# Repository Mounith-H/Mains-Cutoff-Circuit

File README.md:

# Mains High-Low Voltage Cutoff Circuit 🔌

A hardware circuit designed to automatically disconnect mains power during overvoltage (>270V) or undervoltage (<170V) conditions to protect appliances.

---

## Table of Contents
- [Features](#features)
- [Components](#components)
- [Circuit Diagram](#circuit-diagram)
- [How It Works](#how-it-works)
- [Usage](#usage)
- [Safety Notes](#safety-notes)
- [License](#license)
- [Contributing](#contributing)

---

## Features ✨
- **Auto Cutoff**: Disconnects power during voltage fluctuations.
- **4 LED Indicators**: 
  - 1 OverVoltage LED: RED for input has voltage above set threshold, Green for normal.
  - 2 UnderVoltage LED: RED for input has voltage below set threshold, Green for normal.
  - 3 Delay LED: RED for in delay mode.
  - 4 Output LED: RED Output OFF, GREEN Output ON.
- **DELAY ON/OFF**: jumper(J6)) to Enable/Desable dealy.
- **Relay-Based**: Supports high-current loads.

---

## Components 🛠️

| Designators               | Component                      | Footprint                                      | Quantity |  
|---------------------------|--------------------------------|-----------------------------------------------|----------|
| R5, R21, R22, R28, R24, R18 | 10k Resistor                  | Axial DIN0207 (6.3mm x 2.5mm)                | 6        |
| R15, R13, R10, R6, R19, R9, R20, R7, R12, R23, R16 | 1k Resistor          | Axial DIN0207 (6.3mm x 2.5mm)                | 11       |
| U1                        | LM324 Op-Amp IC               | CERDIP-14 (Side-Brazed Socket)               | 1        |
| R17, R11, R14, R8         | 220Ω Resistor                 | Axial DIN0207 (6.3mm x 2.5mm)                | 4        |
| Q4, Q3, Q7, Q2, Q1, Q6    | BC547 Transistor              | TO-92L Wide Package                          | 6        |
| D6, D8, D9, D7            | Dual LED                      | LED D3.0mm-3                                 | 4        |
| D5, D11, D3, D4           | 1N4148 Diode                  | DO-35 Horizontal                             | 4        |
| R4, R25, R2               | 16k Resistor                  | Axial DIN0207 (6.3mm x 2.5mm)                | 3        |
| J4                        | LED Board Header              | 1x06 Pin Header (2.54mm)                     | 1        |
| R1                        | 1.5k Resistor                 | Axial DIN0207 (6.3mm x 2.5mm)                | 1        |
| C2                        | 1µF Capacitor                 | Radial D5.0mm (P2.50mm)                      | 1        |
| RV2, RV1, RV3             | 10k Potentiometer             | Bourns 3296W Vertical Trimmer                | 3        |
| PS1                       | Hi-Link 12V Power Supply      | HLK-5M05 Module                              | 1        |
| D10, D2, D1               | 1N4007 Diode                  | DO-41 Horizontal                             | 3        |
| RV4                       | 5k Potentiometer              | Bourns 3296W Vertical Trimmer                | 1        |
| R26                       | 470k Resistor                 | Axial DIN0207 (6.3mm x 2.5mm)                | 1        |
| C3                        | 100µF Capacitor               | Radial D6.3mm (P2.50mm)                      | 1        |
| F1                        | Fuse                          | Blade ATO (Direct Solder)                    | 1        |
| J2                        | Transformer Terminal Block    | 1x03 Terminal Block (5.00mm)                 | 1        |
| J1, J5                    | AC Input Terminal Block       | Phoenix PT-1.5-2-5.0-H (5.00mm)              | 2        |
| R27                       | 0Ω Jumper Resistor            | Axial DIN0207 (6.3mm x 2.5mm)                | 1        |
| K1                        | Relay (SPDT)                  | SANYOU SRD Series Form-C                     | 1        |
| C1, C4                    | 100nF Capacitor               | 1210 SMD (Hand-Soldered)                     | 2        |
| U2                        | LM78M05 Voltage Regulator     | TO-252-2 Package                             | 1        |

---

## How It Works ⚙️
AC Input → Voltage Sensing → Threshold Comparison → Relay Control → Load Protection  

**Step-by-Step Explanation**

1. AC Input & Isolation
- Mains power (e.g., 220V AC) enters through terminal blocks J1/J5.
- A transformer (connected via J2) steps down the voltage to 12V AC for safe sensing.
- The Hi-Link 12V module (PS1) converts this to 12V DC, while the LM78M05 (U2) regulates it to 5V DC for the control circuitry.

2. Voltage Sensing
- The AC voltage is scaled down using a resistor network (R1, R2, R4, R25, RV1, RV2).
- Potentiometers RV1 and RV2 set the overvoltage (e.g., >270V) and undervoltage (e.g., <170V) thresholds.

3. Threshold Comparison
- The LM324 op-amp (U1) acts as a comparator:
    - One section compares the sensed voltage to the high threshold (set by RV1).
    - Another section compares it to the low threshold (set by RV2).
- If the voltage exceeds either threshold, the LM324 triggers a fault signal.

4. Relay Control
- Fault signals drive BC547 transistors (Q1-Q6) to deactivate the SPDT relay (K1).
- The relay disconnects the load from mains power to prevent damage.

5. Status Indication
- Dual LEDs (D6-D9) indicate system status:
    - Green: Normal operation (voltage within range).
    - Red: Error detected.

- The 470k resistor (R26) and 100µF capacitor (C3) introduce a delay to avoid false triggering.

---

## Usage 🚀  
1. **Power Up**:  
   - Connect mains power to `J1` and load to relay output `J5`.  
2. **Normal Operation**:  
   - **Green LED**: Voltage within safe range (170V–270V).  
3. **Fault Detection**:  
   - **Red LED**: Overvoltage/Undervoltage detected (>270V) or (<170V).  
   - Relay disconnects load automatically.  
4. **Reset**:  
   - **Auto-reset**: Wait for delay (adjustable via `RV4`).  
   - **Manual reset**: Remove short on `J6` pins to restore power immediately.  

---

## Safety Notes ⚠️  
- **High Voltage Risk!** This circuit interacts with mains power.  
  - Use insulated tools and enclosures.  
  - Test with a low-voltage (12V AC) source before connecting to mains.  
- **Fuse Protection**: Ensure `F1` matches your load’s current rating.  
- **No Live Adjustments**: Always power off before adjusting `RV1/RV2/RV3`.  
- **Secure Connections**: Double-check terminal blocks (`J1/J5`) and transformer wiring.  

### Created by [Mounith H] – 📧 mounith.h@gmail.com

## License 📄  
```text
MIT License

Copyright (c) 2023 [Your Name]

Permission is hereby granted, free of charge, to any person obtaining a copy
of this software and associated documentation files (the "Software"), to deal
in the Software without restriction, including without limitation the rights
to use, copy, modify, merge, publish, distribute, sublicense, and/or sell
copies of the Software, and to permit persons to whom the Software is
furnished to do so, subject to the following conditions:

The above copyright notice and this permission notice shall be included in all
copies or substantial portions of the Software.

THE SOFTWARE IS PROVIDED "AS IS", WITHOUT WARRANTY OF ANY KIND, EXPRESS OR
IMPLIED, INCLUDING BUT NOT LIMITED TO THE WARRANTIES OF MERCHANTABILITY,
FITNESS FOR A PARTICULAR PURPOSE AND NONINFRINGEMENT. IN NO EVENT SHALL THE
AUTHORS OR COPYRIGHT HOLDERS BE LIABLE FOR ANY CLAIM, DAMAGES OR OTHER
LIABILITY, WHETHER IN AN ACTION OF CONTRACT, TORT OR OTHERWISE, ARISING FROM,
OUT OF OR IN CONNECTION WITH THE SOFTWARE OR THE USE OR OTHER DEALINGS IN THE
SOFTWARE.

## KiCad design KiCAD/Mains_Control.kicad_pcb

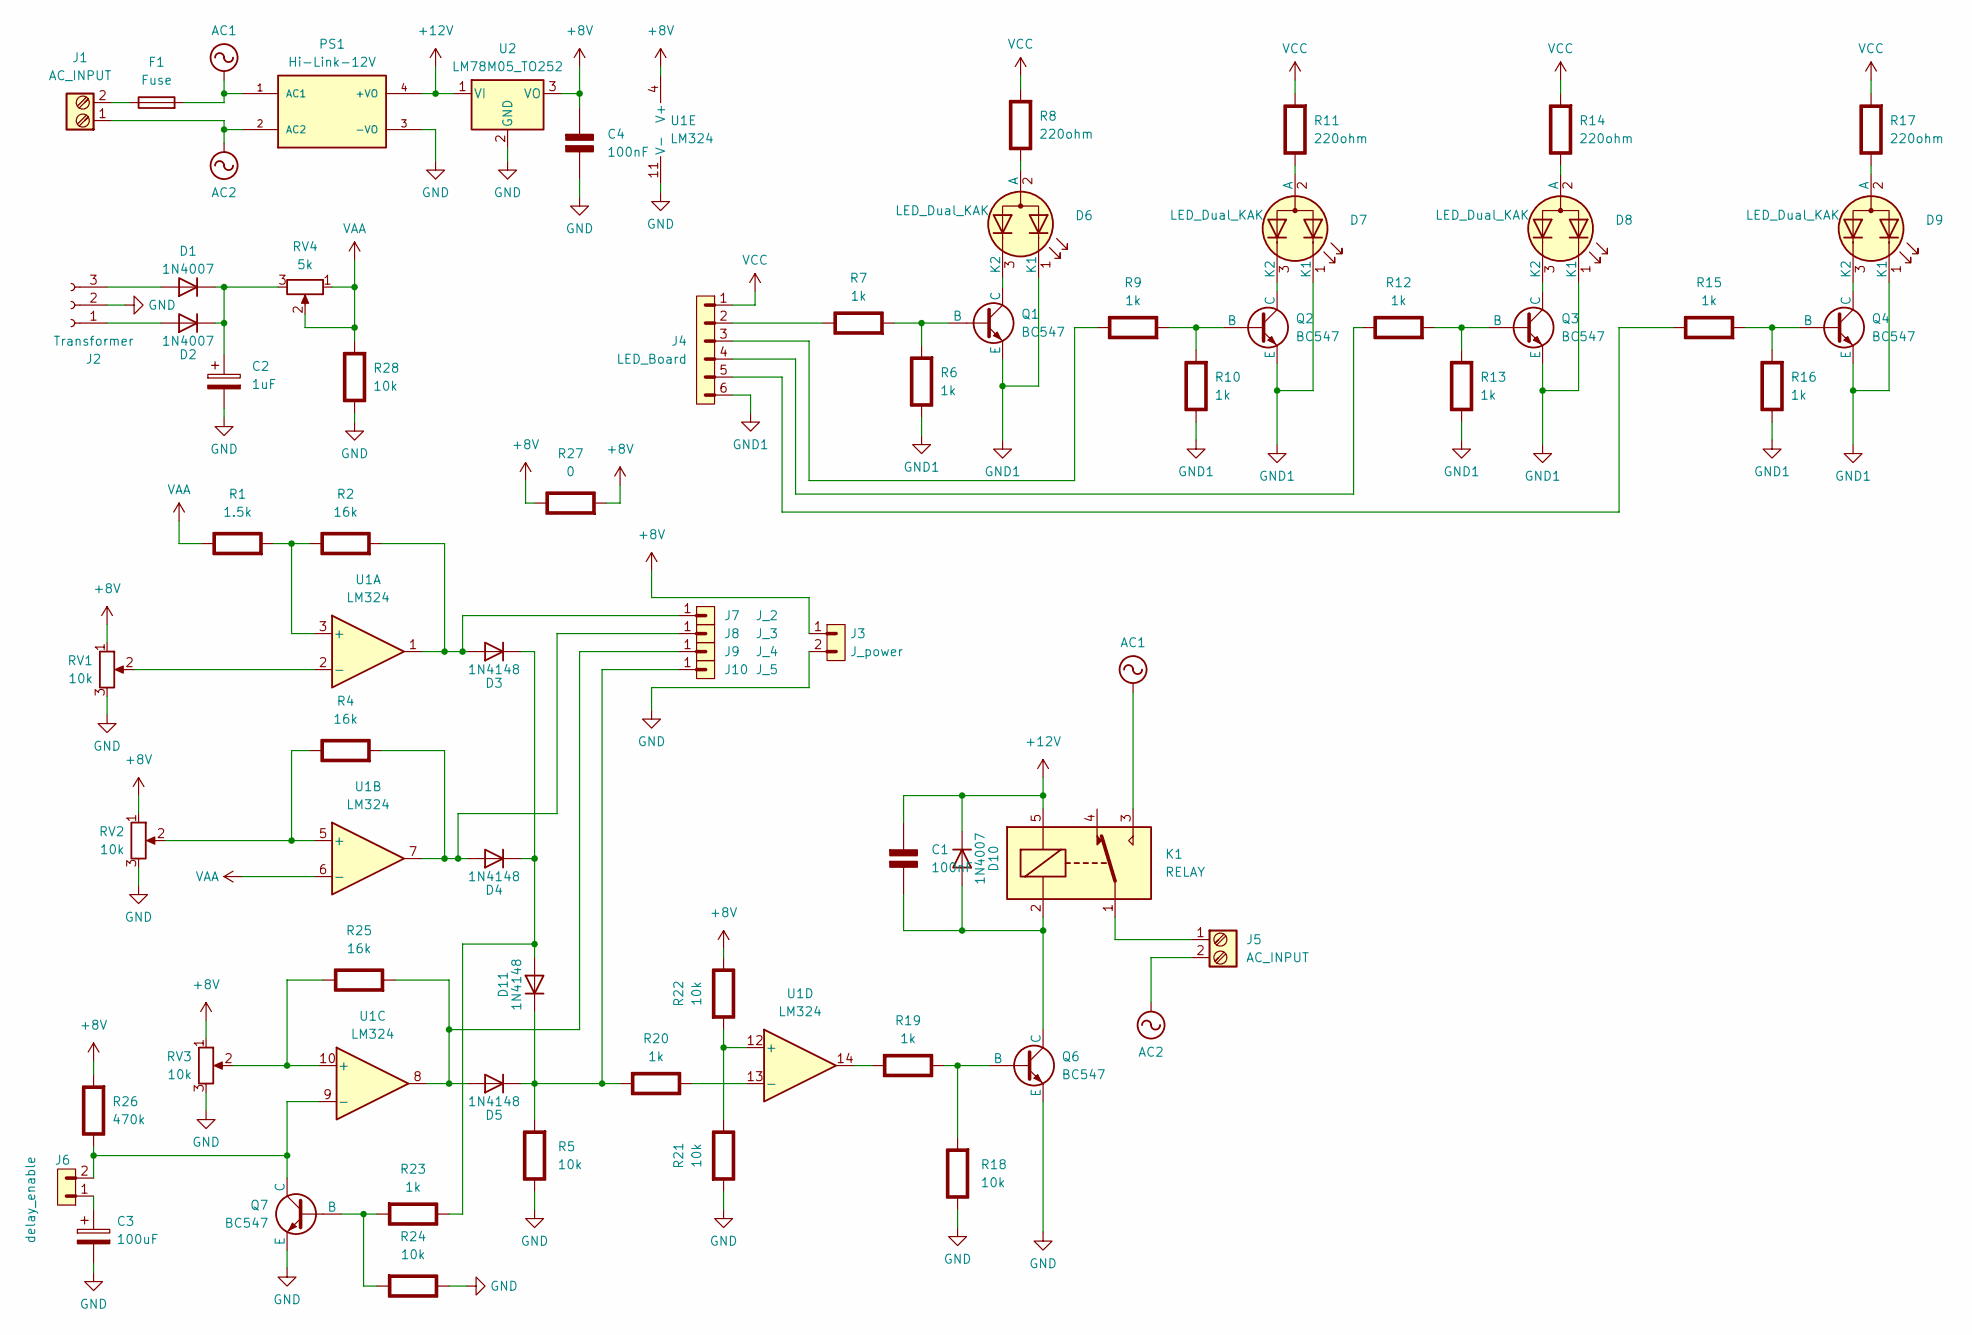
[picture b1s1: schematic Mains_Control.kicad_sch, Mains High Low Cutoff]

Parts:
C1, C4: 100nF; C_1210_3225Metric_Pad1.33x2.70mm_HandSolder; Rating V
C2: 1uF; CP_Radial_D5.0mm_P2.50mm
C3: 100uF; CP_Radial_D6.3mm_P2.50mm
D1, D2, D10: 1N4007; D_A-405_P10.16mm_Horizontal
D3, D4, D5, D11: 1N4148; D_A-405_P10.16mm_Horizontal
D6, D7, D8, D9: LED_Dual_KAK; LED_D3.0mm-3
F1: Fuse; Fuse_Blade_ATO_directSolder
J1, J5: AC_INPUT; TerminalBlock_Phoenix_PT-1,5-2-5.0-H_1x02_P5.00mm_Horizontal
J2: Transformer; TerminalBlock_MaiXu_MX126-5.0-03P_1x03_P5.00mm
J3: J_power; PinHeader_1x02_P2.54mm_Vertical
J4: LED_Board; PinHeader_1x06_P2.54mm_Vertical
J6: delay_enable; PinHeader_1x02_P2.54mm_Vertical
J7: J_2; PinHeader_1x01_P2.54mm_Vertical
J8: J_3; PinHeader_1x01_P2.54mm_Vertical
J9: J_4; PinHeader_1x01_P2.54mm_Vertical
J10: J_5; PinHeader_1x01_P2.54mm_Vertical
K1: RELAY; Relay_SPDT_SANYOU_SRD_Series_Form_C
PS1: Hi-Link-12V; HLK-5M05_CONV_HLK-5M05
Q1, Q2, Q3, Q4, Q6, Q7: BC547; TO-92L_Wide
R1: 1.5k; R_Axial_DIN0207_L6.3mm_D2.5mm_P10.16mm_Horizontal; Rating W
R2, R4, R25: 16k; R_Axial_DIN0207_L6.3mm_D2.5mm_P10.16mm_Horizontal; Rating W
R5, R18, R21, R22, R24, R28: 10k; R_Axial_DIN0207_L6.3mm_D2.5mm_P10.16mm_Horizontal; Rating W
R6, R7, R9, R10, R12, R13, R15, R16, R19, R20, R23: 1k; R_Axial_DIN0207_L6.3mm_D2.5mm_P10.16mm_Horizontal; Rating W
R8, R11, R14, R17: 220ohm; R_Axial_DIN0207_L6.3mm_D2.5mm_P10.16mm_Horizontal; Rating W
R26: 470k; R_Axial_DIN0207_L6.3mm_D2.5mm_P10.16mm_Horizontal; Rating W
R27: 0; R_Axial_DIN0207_L6.3mm_D2.5mm_P10.16mm_Horizontal; Rating W
RV1, RV2, RV3: 10k; Potentiometer_Bourns_3296W_Vertical
RV4: 5k; Potentiometer_Bourns_3296W_Vertical
U1: LM324; CERDIP-14_W7.62mm_SideBrazed_LongPads_Socket
U2: LM78M05_TO252; TO-252-2

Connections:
+8V: C4.1 (+), J3.1, R22.1 (+), R26.2 (-), R27.1 (+), R27.2 (-), RV1.1, RV2.1, RV3.1, U1.4 (V+), U2.3 (VO)
+12V: C1.1 (+), D10.1 (K), K1.5, PS1.4 (+VO), U2.1 (VI)
AC1: F1.2, K1.3, PS1.1 (AC1)
AC2: J1.1, J5.2, PS1.2 (AC2)
GND: C2.2, C3.2, C4.2 (-), J2.2, J3.2, PS1.3 (-VO), Q6.3 (E), Q7.3 (E), R5.1 (+), R18.1 (+), R21.2 (-), R24.1 (+), R28.1 (+), RV1.3, RV2.3, RV3.3, U1.11 (V-), U2.2 (GND)
GND1: D6.1 (K1), D7.1 (K1), D8.1 (K1), D9.1 (K1), J4.6, Q1.3 (E), Q2.3 (E), Q3.3 (E), Q4.3 (E), R6.1 (+), R10.1 (+), R13.1 (+), R16.1 (+)
unnamed: C1.2 (-), D10.2 (A), K1.2, Q6.1 (C)
unnamed: C3.1, J6.1
unnamed: D1.2 (A), J2.3
unnamed: C2.1, D1.1 (K), D2.1 (K), RV4.3
unnamed: D2.2 (A), J2.1
unnamed: D3.2 (A), J7.1, R2.2 (-), U1.1
unnamed: D4.2 (A), J8.1, R4.2 (-), U1.7
unnamed: D5.2 (A), J9.1, R25.2 (-), U1.8
unnamed: D6.2 (A), R8.1 (+)
unnamed: D6.3 (K2), Q1.1 (C)
unnamed: D7.2 (A), R11.1 (+)
unnamed: D7.3 (K2), Q2.1 (C)
unnamed: D8.2 (A), R14.1 (+)
unnamed: D8.3 (K2), Q3.1 (C)
unnamed: D9.2 (A), R17.1 (+)
unnamed: D9.3 (K2), Q4.1 (C)
unnamed: D3.1 (K), D4.1 (K), D11.2 (A), R23.1 (+)
unnamed: D5.1 (K), D11.1 (K), J10.1, R5.2 (-), R20.2 (-)
unnamed: F1.1, J1.2
unnamed: J5.1, K1.1
unnamed: Q1.2 (B), R6.2 (-), R7.2 (-)
unnamed: Q2.2 (B), R9.2 (-), R10.2 (-)
unnamed: Q3.2 (B), R12.2 (-), R13.2 (-)
unnamed: Q4.2 (B), R15.2 (-), R16.2 (-)
unnamed: Q6.2 (B), R18.2 (-), R19.1 (+)
unnamed: Q7.2 (B), R23.2 (-), R24.2 (-)
unnamed: J6.2, Q7.1 (C), R26.1 (+), U1.9 (-)
unnamed: R1.2 (-), R2.1 (+), U1.3 (+)
unnamed: R4.1 (+), RV2.2, U1.5 (+)
unnamed: J4.2, R7.1 (+)
unnamed: J4.3, R9.1 (+)
unnamed: J4.4, R12.1 (+)
unnamed: J4.5, R15.1 (+)
unnamed: R19.2 (-), U1.14
unnamed: R20.1 (+), U1.13 (-)
unnamed: R21.1 (+), R22.2 (-), U1.12 (+)
unnamed: R25.1 (+), RV3.2, U1.10 (+)
unnamed: RV1.2, U1.2 (-)
VAA: R1.1 (+), R28.2 (-), RV4.1, RV4.2, U1.6 (-)
VCC: J4.1, R8.2 (-), R11.2 (-), R14.2 (-), R17.2 (-)

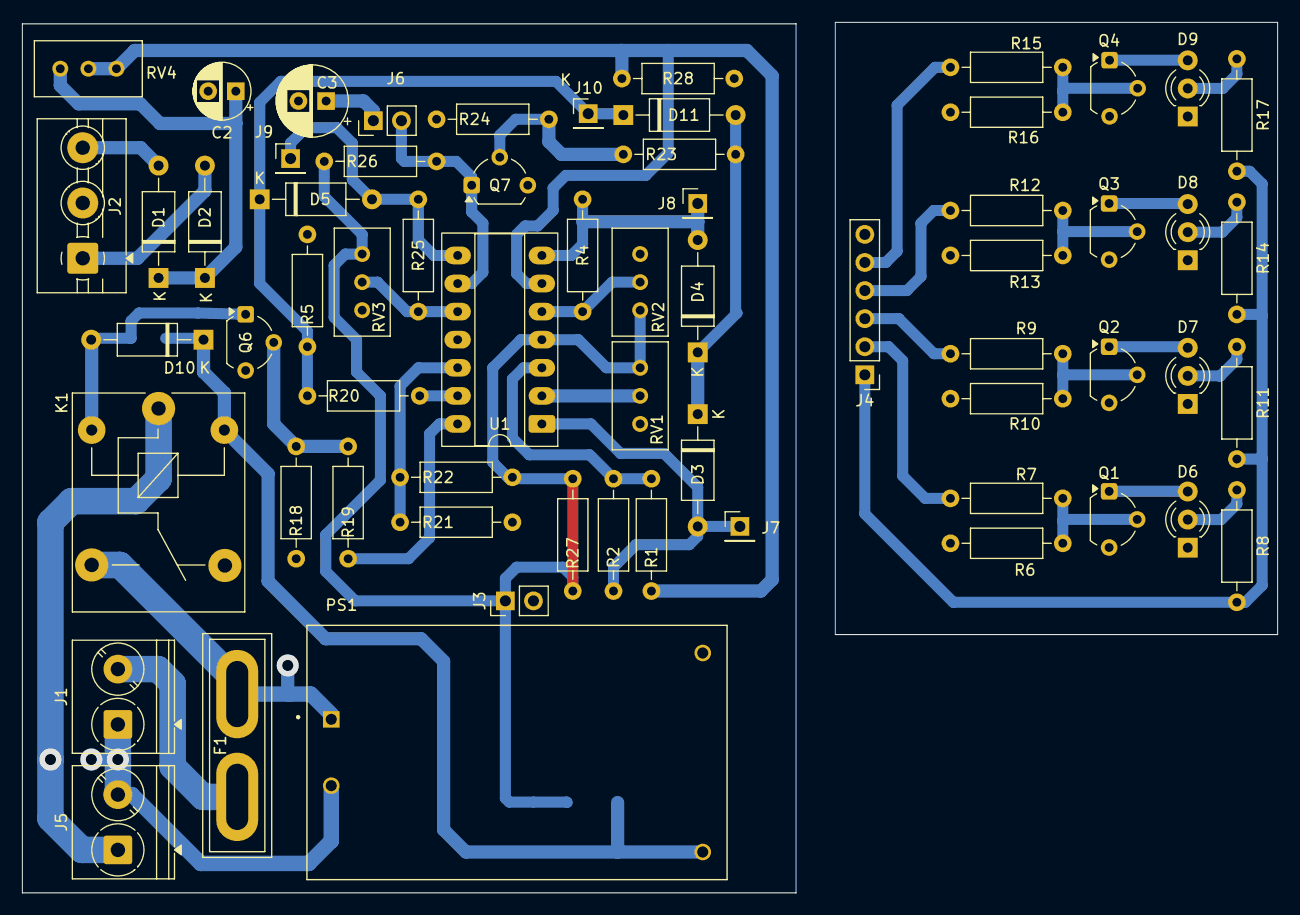
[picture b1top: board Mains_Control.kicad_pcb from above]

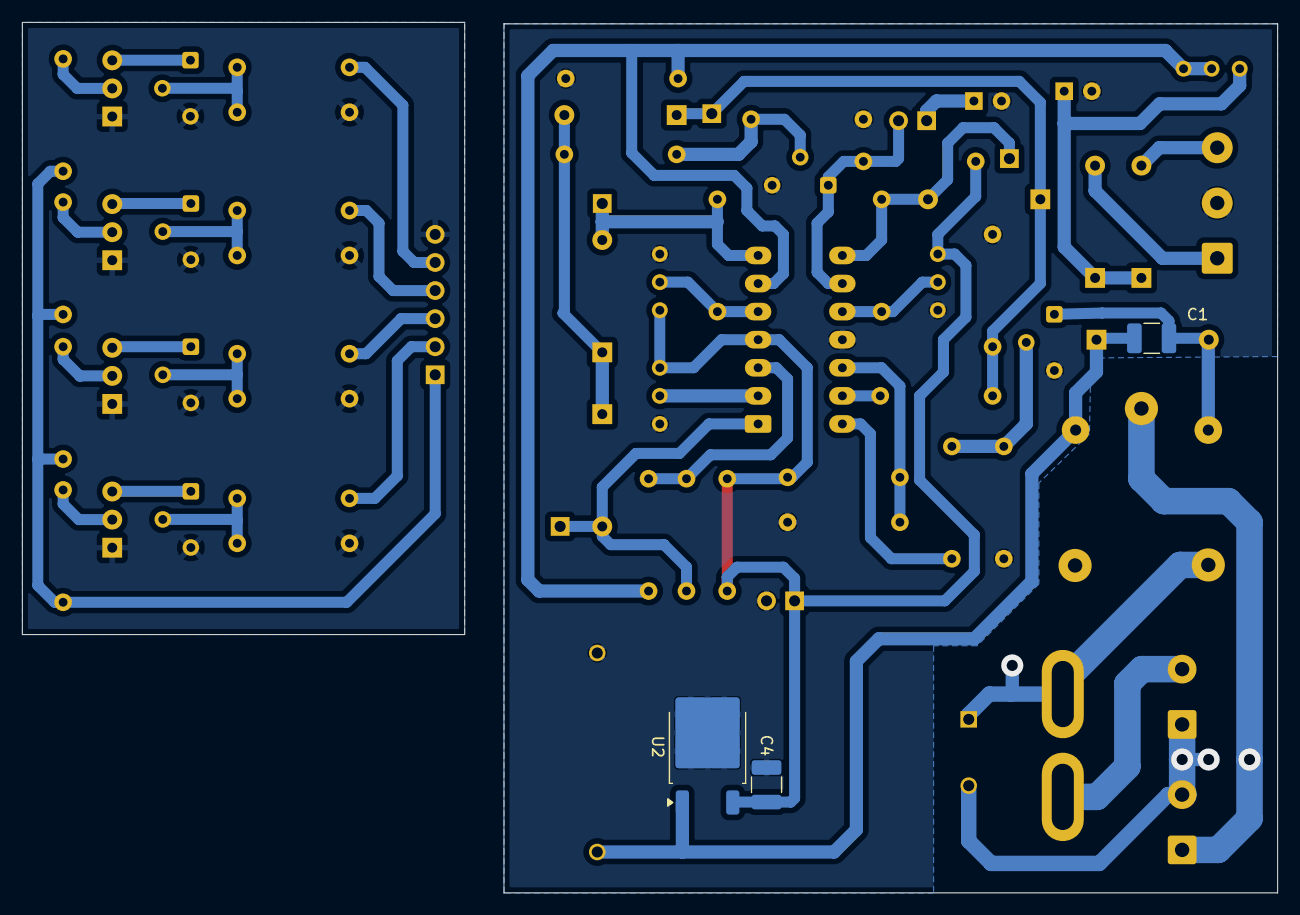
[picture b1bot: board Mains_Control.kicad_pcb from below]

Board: 2 copper layers, 113.5 x 78.7 mm, 67 parts (3 on the bottom side), 46 nets.

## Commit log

2025-04-18 Initial commit: Mains High-Low Cutoff Circuit
